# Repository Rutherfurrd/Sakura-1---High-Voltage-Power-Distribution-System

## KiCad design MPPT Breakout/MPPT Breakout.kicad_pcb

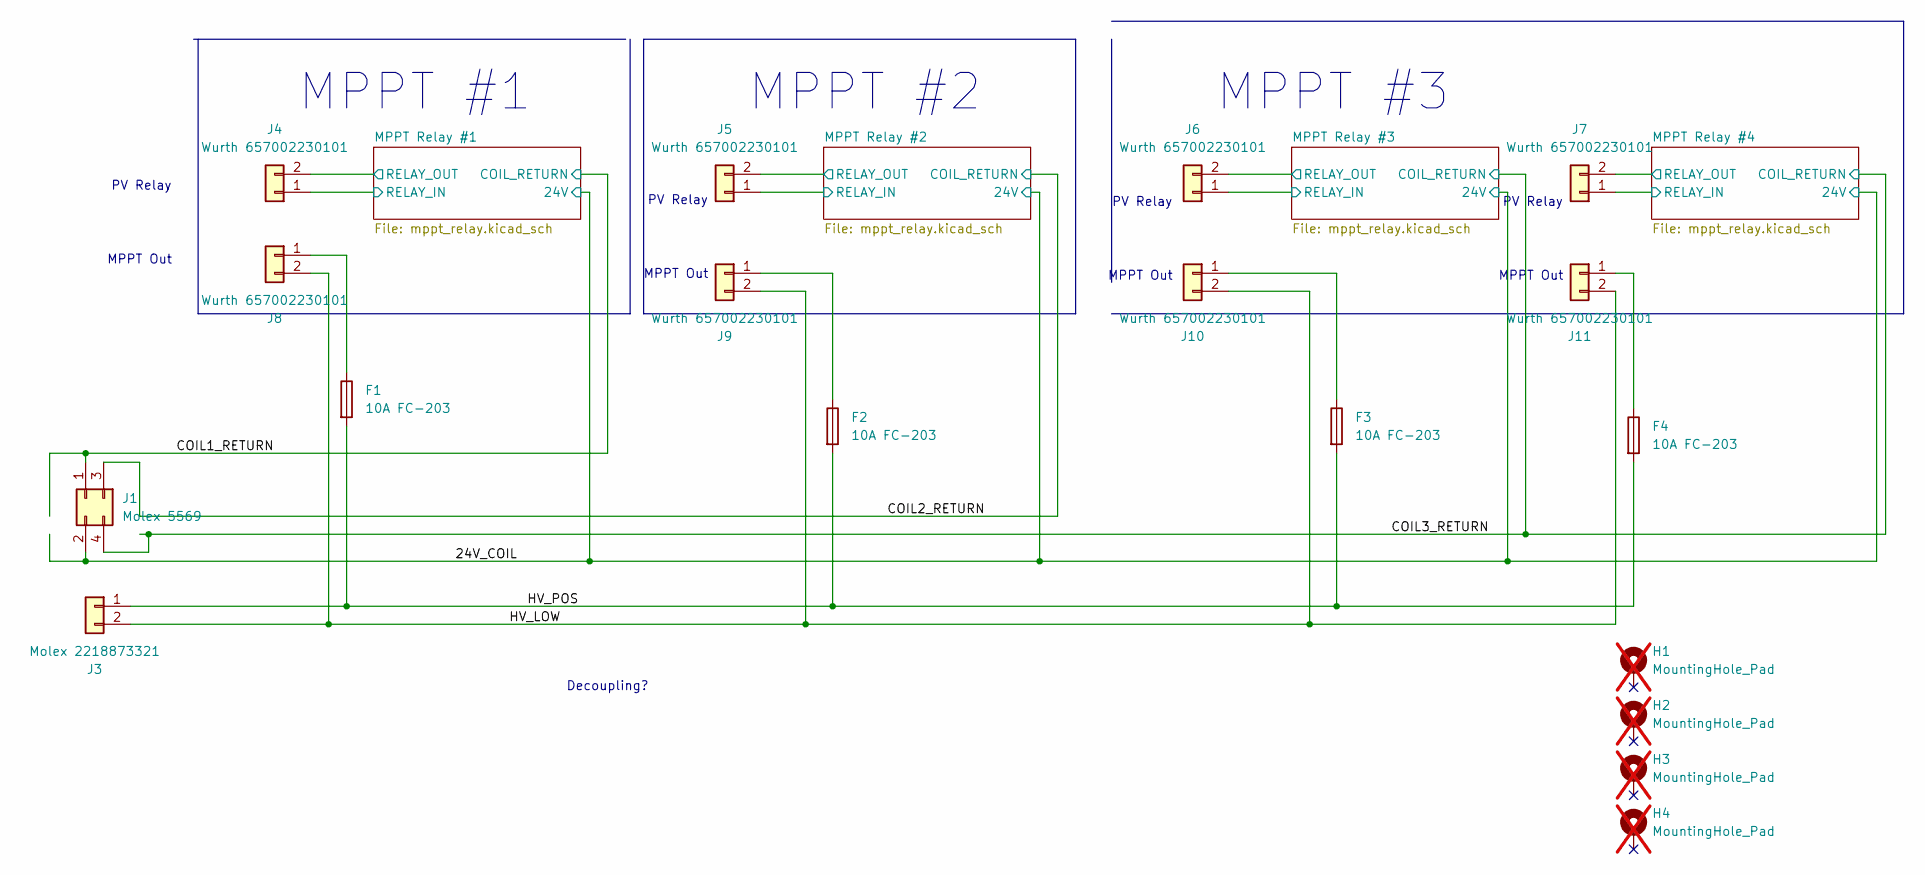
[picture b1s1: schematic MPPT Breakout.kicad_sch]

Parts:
F1, F2, F3, F4: 10A FC-203; Fuseholder_Clip-5x20mm_Bel_FC-203-22_Lateral_P17.80x5.00mm_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; Digikey SID 5923-FC-203BRIGHTTIN-ND
H1, H2, H3, H4: MountingHole_Pad; MountingHole_3.2mm_M3_DIN965_Pad_TopBottom; not fitted
J1: Molex 5569; Molex_Mini-Fit_Jr_5569-04A2_2x02_P4.20mm_Horizontal; Digikey SID WM23323-ND
J3: Molex 2218873321; CONN_2218873321_KEYOPT1_02P_MOL; Digikey SID 900-2218873321-ND
J4, J5, J6, J7, J8, J9, J10, J11: Wurth 657002230101; 657002230101; Digikey SID 732-657002230101-ND

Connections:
/24V_COIL: J1.2 (Pin_3); also elsewhere on the board
/COIL1_RETURN: J1.1 (Pin_2); also elsewhere on the board
/COIL2_RETURN: J1.3 (Pin_1); also elsewhere on the board
/COIL3_RETURN: J1.4; also elsewhere on the board
/HV_LOW: J3.2, J8.2, J9.2, J10.2, J11.2
/HV_POS: F1.2, F2.2, F3.2, F4.2, J3.1
/MPPT Relay #1/RELAY_IN: J4.1; also elsewhere on the board
/MPPT Relay #1/RELAY_OUT: J4.2; also elsewhere on the board
/MPPT Relay #2/RELAY_IN: J5.1; also elsewhere on the board
/MPPT Relay #2/RELAY_OUT: J5.2; also elsewhere on the board
/MPPT Relay #3/RELAY_IN: J6.1; also elsewhere on the board
/MPPT Relay #3/RELAY_OUT: J6.2; also elsewhere on the board
/MPPT Relay #4/RELAY_IN: J7.1; also elsewhere on the board
/MPPT Relay #4/RELAY_OUT: J7.2; also elsewhere on the board
unnamed: F1.1, J8.1
unnamed: F2.1, J9.1
unnamed: F3.1, J10.1
unnamed: F4.1, J11.1

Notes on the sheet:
MPPT Out
Decoupling?
MPPT #3
PV Relay
MPPT #1
MPPT #2

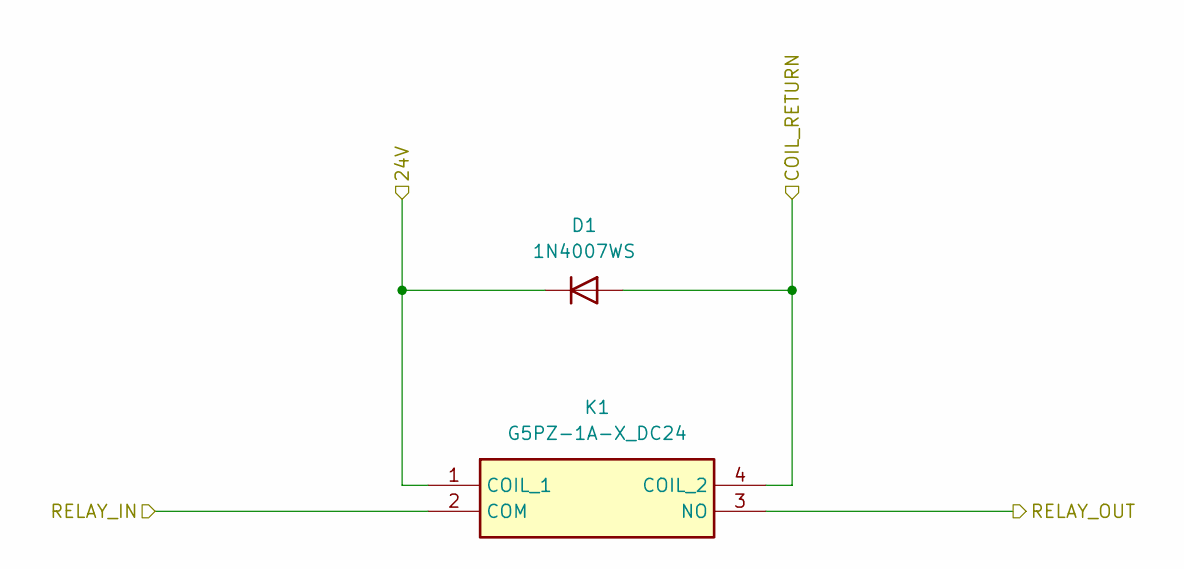
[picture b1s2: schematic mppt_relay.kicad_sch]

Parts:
D1: 1N4007WS; D_SOD-323_HandSoldering; Digikey SID 5399-1N4007WSCT-ND
K1: G5PZ-1A-X_DC24; G5PZ1AXDC24; Mouser Part Number 653-G5PZ-1A-XDC24

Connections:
/24V_COIL: D1.1 (K), K1.1 (COIL_1); also elsewhere on the board
/COIL1_RETURN: D1.2 (A), K1.4 (COIL_2); also elsewhere on the board
/MPPT Relay #1/RELAY_IN: K1.2 (COM); also elsewhere on the board
/MPPT Relay #1/RELAY_OUT: K1.3 (NO); also elsewhere on the board

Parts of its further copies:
D2, D3, D4: 1N4007WS; D_SOD-323_HandSoldering; Digikey SID 5399-1N4007WSCT-ND
K2, K3, K4: G5PZ-1A-X_DC24; G5PZ1AXDC24; Mouser Part Number 653-G5PZ-1A-XDC24

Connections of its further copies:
/24V_COIL: D2.1 (K), D3.1 (K), D4.1 (K), K2.1 (COIL_1), K3.1 (COIL_1), K4.1 (COIL_1); also elsewhere on the board
/COIL2_RETURN: D2.2 (A), K2.4 (COIL_2); also elsewhere on the board
/COIL3_RETURN: D3.2 (A), D4.2 (A), K3.4 (COIL_2), K4.4 (COIL_2); also elsewhere on the board
/MPPT Relay #2/RELAY_IN: K2.2 (COM); also elsewhere on the board
/MPPT Relay #2/RELAY_OUT: K2.3 (NO); also elsewhere on the board
/MPPT Relay #3/RELAY_IN: K3.2 (COM); also elsewhere on the board
/MPPT Relay #3/RELAY_OUT: K3.3 (NO); also elsewhere on the board
/MPPT Relay #4/RELAY_IN: K4.2 (COM); also elsewhere on the board
/MPPT Relay #4/RELAY_OUT: K4.3 (NO); also elsewhere on the board

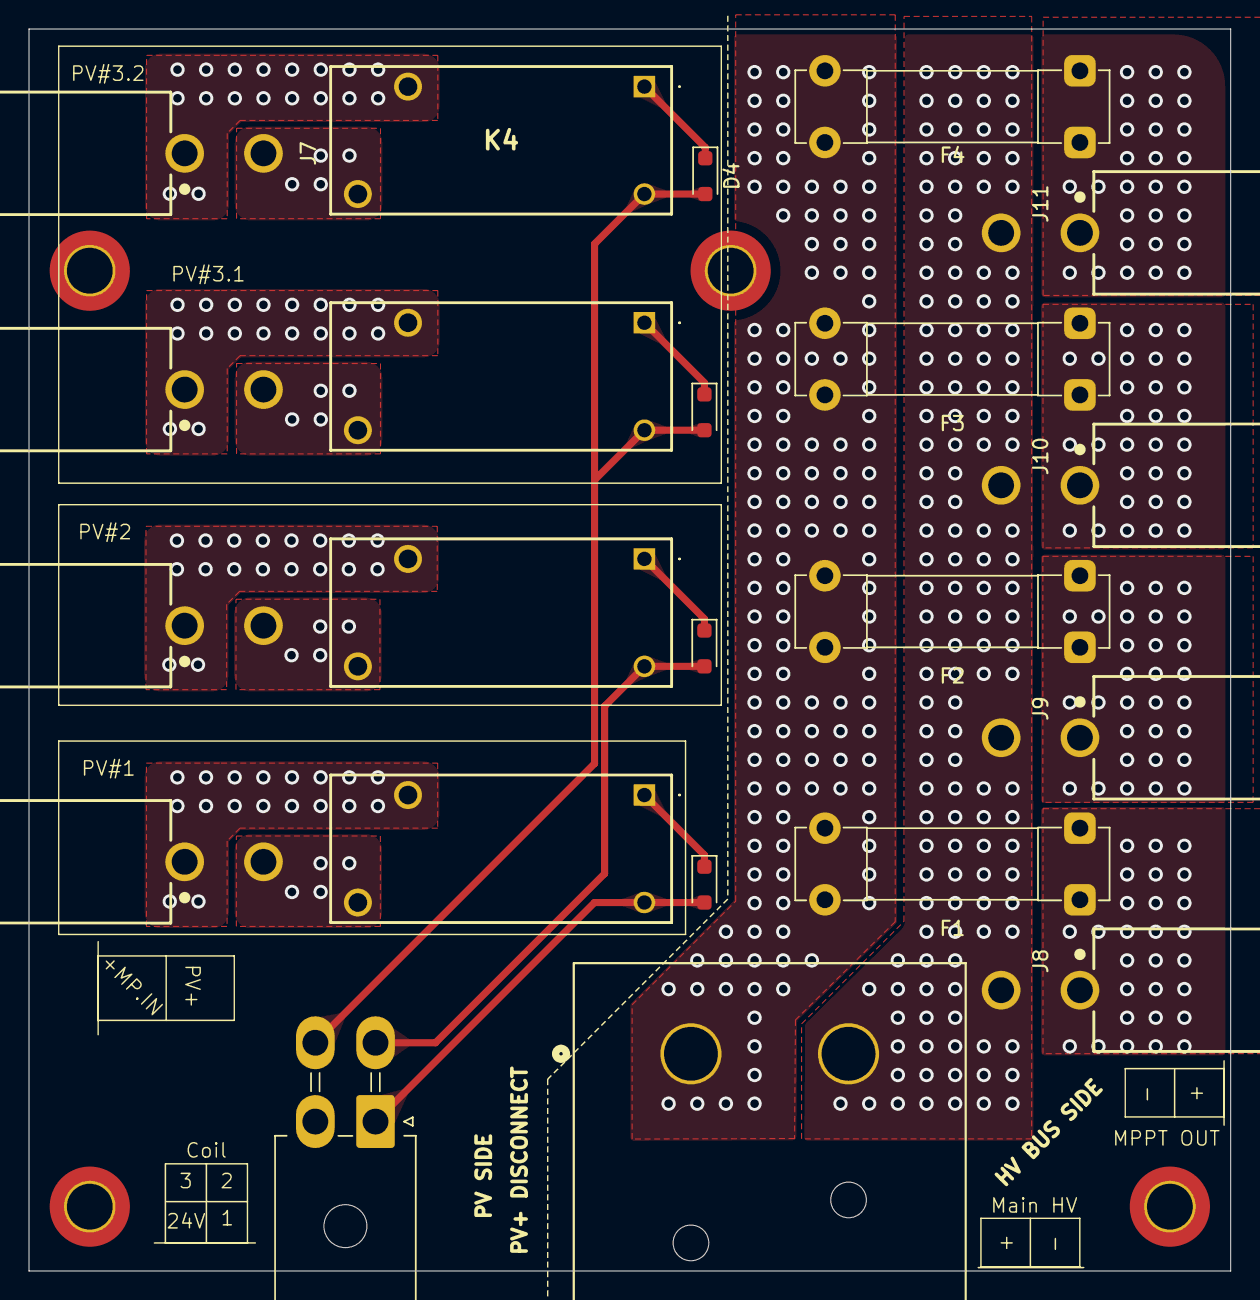
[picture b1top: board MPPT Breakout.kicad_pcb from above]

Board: 4 copper layers, 83.9 x 86.7 mm, 26 parts (0 on the bottom side), 18 nets.

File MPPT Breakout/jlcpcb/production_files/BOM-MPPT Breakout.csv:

Comment,Designator,Footprint,LCSC,Quantity
Wurth 657002230101,J5,657002230101,,1
10A FC-203,F3,Fuseholder_Clip-5x20mm_Bel_FC-203-22_Lateral_P17.80x5.00mm_D1.17mm_Horizontal,,1
10A FC-203,F1,Fuseholder_Clip-5x20mm_Bel_FC-203-22_Lateral_P17.80x5.00mm_D1.17mm_Horizontal,,1
1N4007WS,D2,D_SOD-323_HandSoldering,,1
Wurth 657002230101,J4,657002230101,,1
Wurth 657002230101,J6,657002230101,,1
Molex 2218873321,J3,CONN_2218873321_KEYOPT1_02P_MOL,,1
10A FC-203,F2,Fuseholder_Clip-5x20mm_Bel_FC-203-22_Lateral_P17.80x5.00mm_D1.17mm_Horizontal,,1
Molex 5569,J1,Molex_Mini-Fit_Jr_5569-04A2_2x02_P4.20mm_Horizontal,,1
1N4007WS,D3,D_SOD-323_HandSoldering,,1
1N4007WS,D1,D_SOD-323_HandSoldering,,1
1N4007WS,D4,D_SOD-323_HandSoldering,,1
10A FC-203,F4,Fuseholder_Clip-5x20mm_Bel_FC-203-22_Lateral_P17.80x5.00mm_D1.17mm_Horizontal,,1
Wurth 657002230101,J7,657002230101,,1
Wurth 657002230101,J8,657002230101,,1
Wurth 657002230101,J10,657002230101,,1
Wurth 657002230101,J11,657002230101,,1
Wurth 657002230101,J9,657002230101,,1

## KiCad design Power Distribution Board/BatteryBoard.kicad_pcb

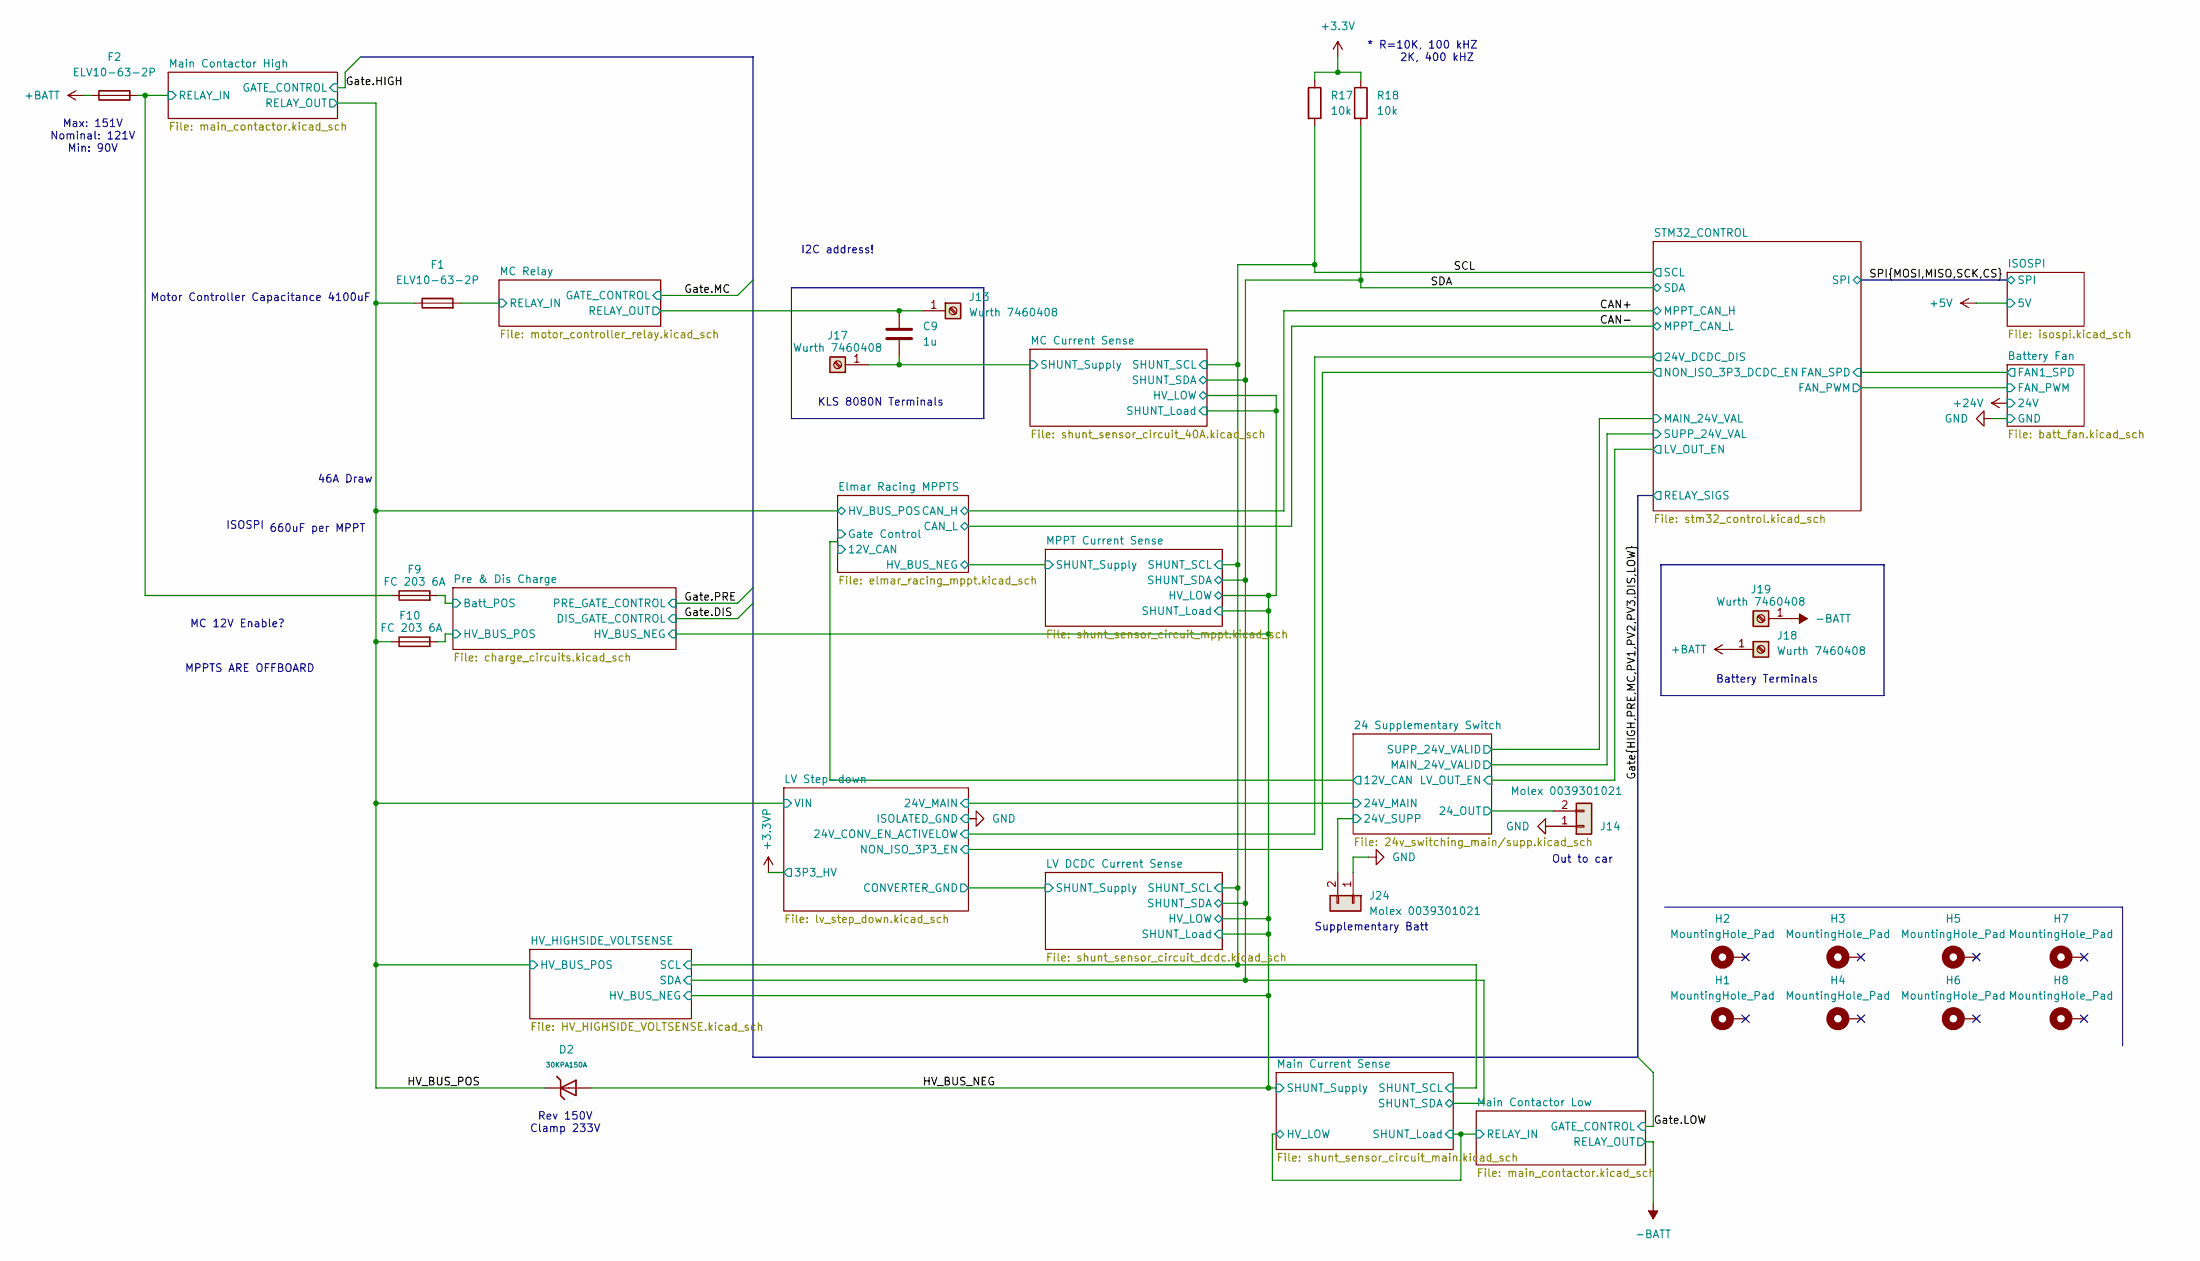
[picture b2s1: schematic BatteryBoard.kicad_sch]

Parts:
C9: 1u; C_1812_4532Metric; LCSC C3037685
D2: 30KPA150A; D_P600_R-6_P7.62mm_Vertical_AnodeUp; DigiKey_Part_Number 30KPA150ACT-ND
F1, F2: ELV10-63-2P; ELV10-XX-2P; DigiKey_Part_Number 283-ELV10-63-2P-ND
F9, F10: FC 203 6A; Fuseholder_Clip-5x20mm_Bel_FC-203-22_Lateral_P17.80x5.00mm_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; DigiKey_Part_Number 5923-FC-203BRIGHTTIN-ND
H1, H2, H3, H4, H5, H6, H7, H8: MountingHole_Pad; MountingHole_3.2mm_M3_DIN965_Pad_TopBottom
J13, J17, J18, J19: Wurth 7460408; MP_Wurth_WP-BUCF_7460408; DigiKey_Part_Number 732-7460408-ND
J14, J24: Molex 0039301021; Molex_Mini-Fit_Jr_5566-02A_2x01_P4.20mm_Vertical; DigiKey_Part_Number WM3843-ND
R17, R18: 10k; R_0603_1608Metric_Pad0.98x0.95mm_HandSolder; Rating 75V; LCSC C95204

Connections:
+3.3V: R17.1, R18.1; also elsewhere on the board
+BATT: F2.1, J18.1 (Pin_1_1)
-BATT: J19.1 (Pin_1_1); also elsewhere on the board
/24 Supplementary Switch/24V_SUPP: J24.2; also elsewhere on the board
/24 Supplementary Switch/24_OUT: J14.2; also elsewhere on the board
/<NO NET>: R17.2; also elsewhere on the board
/HV_BUS_NEG: D2.2; also elsewhere on the board
/HV_BUS_POS: D2.1, F1.1, F10.1; also elsewhere on the board
/MC Current Sense/SHUNT_Supply: C9.2, J17.1 (Pin_1_1); also elsewhere on the board
/MC Relay/RELAY_IN: F1.2; also elsewhere on the board
/MC Relay/RELAY_OUT: C9.1, J13.1 (Pin_1_1); also elsewhere on the board
/Main Contactor High/RELAY_IN: F2.2, F9.1; also elsewhere on the board
/Pre & Dis Charge/Batt_POS: F9.2; also elsewhere on the board
/Pre & Dis Charge/HV_BUS_POS: F10.2; also elsewhere on the board
/SDA: R18.2; also elsewhere on the board
GND: J14.1, J24.1; also elsewhere on the board

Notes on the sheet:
ISOSPI
MPPTS ARE OFFBOARD
Supplementary Batt
Out to car
MC 12V Enable?
Motor Controller Capacitance 4100uF
I2C address!
660uF per MPPT
Rev 150V Clamp 233V
* R=10K, 100 kHZ 2K, 400 kHZ
KLS 8080N Terminals
Max: 151V Nominal: 121V Min: 90V
Battery Terminals
46A Draw

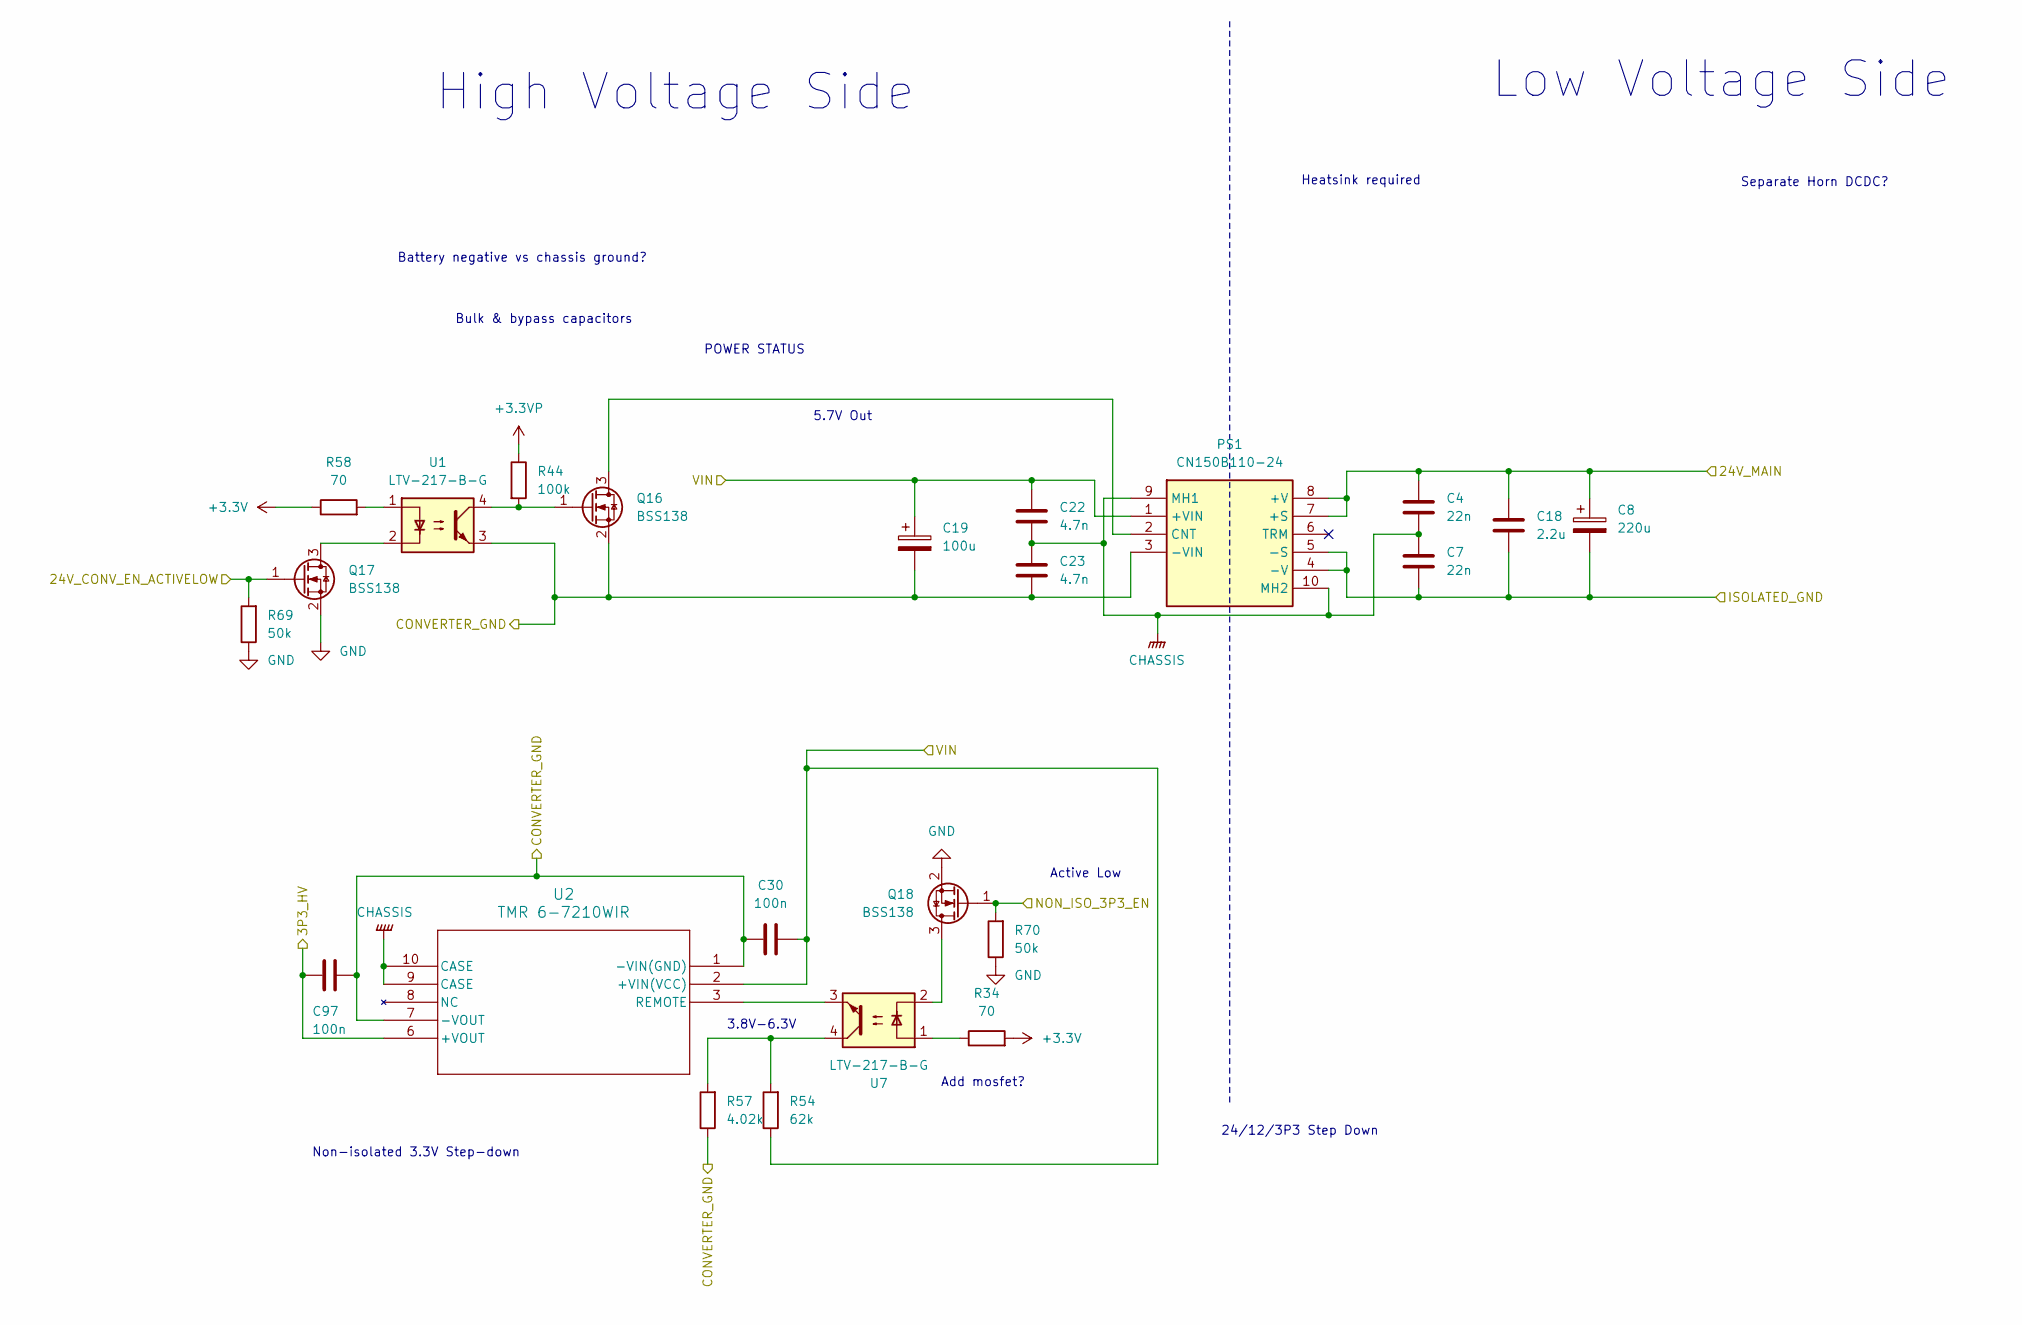
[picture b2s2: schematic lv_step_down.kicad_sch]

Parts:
C4, C7: 22n; R_0805_2012Metric; LCSC C1729
C8: 220u; CP_Radial_D10.0mm_P5.00mm; DigiKey_Part_Number CAP ALUM 220UF 20% 50V RADIAL TH
C18: 2.2u; C_0805_2012Metric_Pad1.18x1.45mm_HandSolder; LCSC C377773
C19: 100u; CP_Radial_D16.0mm_P7.50mm; DigiKey_Part_Number UCS2E101MHD
C22, C23: 4.7n; C_1206_3216Metric_Pad1.33x1.80mm_HandSolder; LCSC C106075
C30: 100n; C_1206_3216Metric_Pad1.33x1.80mm_HandSolder; LCSC C76671
C97: 100n; C_0603_1608Metric_Pad1.08x0.95mm_HandSolder; Rating 50V; LCSC C14663
PS1: CN150B110-24; CN100B11024; Mouser Part Number 967-CN100B110-24
Q16, Q17, Q18: BSS138; SOT-23; LCSC C7420339
R34, R58: 70; R_0603_1608Metric_Pad0.98x0.95mm_HandSolder; Rating 70V; LCSC C4275
R44: 100k; R_0603_1608Metric_Pad0.98x0.95mm_HandSolder; LCSC C25803
R54: 62k; C_0603_1608Metric_Pad1.08x0.95mm_HandSolder; Rating 200V; LCSC C403521
R57: 4.02k; R_0603_1608Metric_Pad0.98x0.95mm_HandSolder; Rating 75V; LCSC C242164
R69, R70: 50k; R_0603_1608Metric_Pad0.98x0.95mm_HandSolder; Rating 70V; LCSC C23184
U1, U7: LTV-217-B-G; SOP-4_4.4x2.6mm_P1.27mm; Part LTV-217-B-G; LCSC C115450
U2: TMR 6-7210WIR; TMR6WIR-SINGLE_TRP; DigiKey_Part_Number 1951-2031-ND

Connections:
+3.3V: R34.2, R58.1; also elsewhere on the board
+3.3VP: C97.2, R44.1, U2.6 (+VOUT); also elsewhere on the board
/24 Supplementary Switch/24V_MAIN: C4.1, C8.1, C18.1, PS1.7 (+S), PS1.8 (+V); also elsewhere on the board
/HV_BUS_POS: C19.1, C22.1, C30.1, PS1.1 (+VIN), R54.1, U2.2 (+VIN(VCC)); also elsewhere on the board
/LV DCDC Current Sense/SHUNT_Supply: C19.2, C23.2, C30.2, C97.1, PS1.3 (-VIN), Q16.2 (S), R57.1, U1.3, U2.1 (-VIN(GND)), U2.7 (-VOUT); also elsewhere on the board
/LV Step-down/24V_CONV_EN_ACTIVELOW: Q17.1 (G), R69.2; also elsewhere on the board
/LV Step-down/NON_ISO_3P3_EN: Q18.1 (G), R70.2; also elsewhere on the board
CHASSIS: C4.2, C7.1, C22.2, C23.1, PS1.9 (MH1), PS1.10 (MH2), U2.9 (CASE), U2.10 (CASE)
GND: C7.2, C8.2, C18.2, PS1.4 (-V), PS1.5 (-S), Q17.2 (S), Q18.2 (S), R69.1, R70.1; also elsewhere on the board
unnamed: PS1.2 (CNT), Q16.3 (D)
unnamed: Q16.1 (G), R44.2, U1.4
unnamed: Q17.3 (D), U1.2
unnamed: Q18.3 (D), U7.2
unnamed: R34.1, U7.1
unnamed: R54.2, R57.2, U7.4
unnamed: R58.2, U1.1
unnamed: U2.3 (REMOTE), U7.3

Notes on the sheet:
Active Low
Separate Horn DCDC?
Bulk & bypass capacitors
High Voltage Side
24/12/3P3 Step Down
Low Voltage Side
Battery negative vs chassis ground?
Add mosfet?
POWER STATUS
3.8V-6.3V
Non-isolated 3.3V Step-down
Heatsink required
5.7V Out

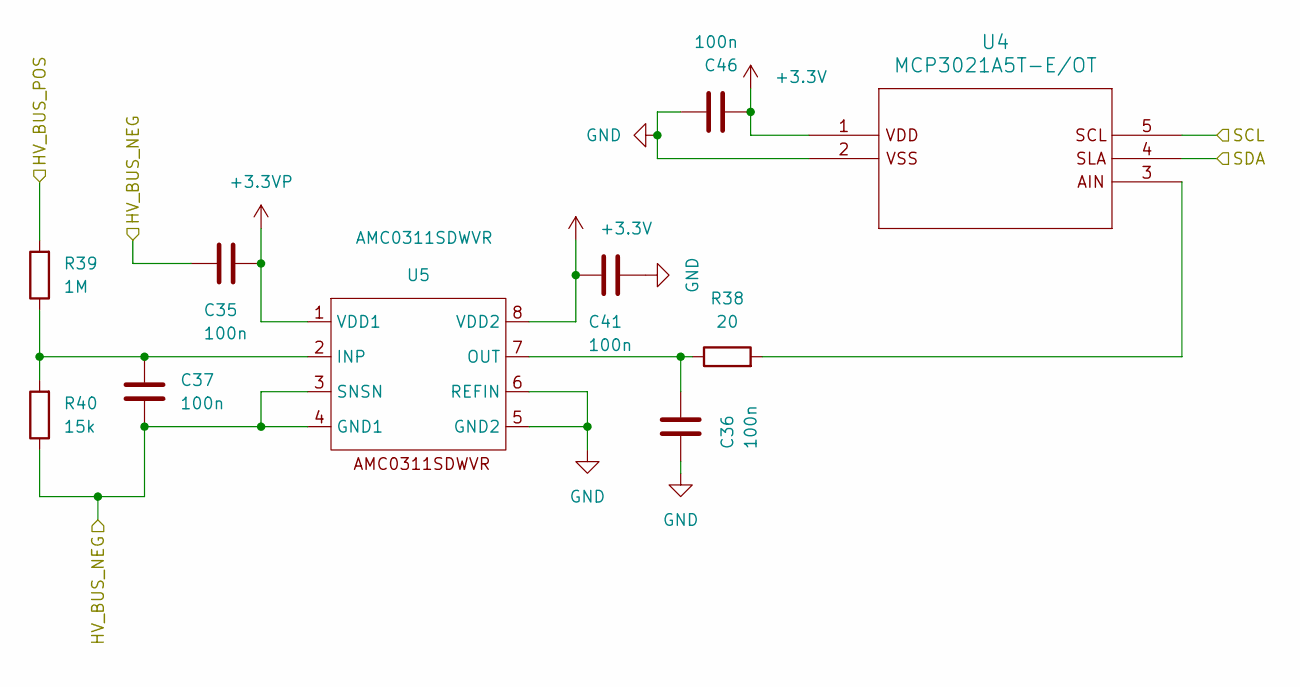
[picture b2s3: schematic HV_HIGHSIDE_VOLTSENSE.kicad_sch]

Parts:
C35, C36, C37, C41, C46: 100n; C_0603_1608Metric_Pad1.08x0.95mm_HandSolder; Rating 50V; LCSC C14663
R38: 20; R_0603_1608Metric_Pad0.98x0.95mm_HandSolder; Rating 75V; LCSC C22950
R39: 1M; R_1206_3216Metric_Pad1.30x1.75mm_HandSolder; Rating 200V; LCSC C17927
R40: 15k; C_0805_2012Metric; Rating 200V; LCSC C17475
U4: MCP3021A5T-E/OT; SOT-23-5; LCSC C128576
U5: AMC0311SDWVR; DWV0008A; LCSC C44211429

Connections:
+3.3V: C41.2, C46.2, U4.1, U5.8 (VDD2); also elsewhere on the board
+3.3VP: C35.1, U5.1 (VDD1); also elsewhere on the board
/<NO NET>: U4.5; also elsewhere on the board
/HV_BUS_NEG: C35.2, C37.2, R40.1, U5.3 (SNSN), U5.4 (GND1); also elsewhere on the board
/HV_BUS_POS: R39.2; also elsewhere on the board
/SDA: U4.4; also elsewhere on the board
GND: C36.2, C41.1, C46.1, U4.2, U5.5 (GND2), U5.6 (REFIN); also elsewhere on the board
unnamed: R38.2, U4.3
unnamed: C37.1, R39.1, R40.2, U5.2 (INP)
unnamed: C36.1, R38.1, U5.7 (OUT)

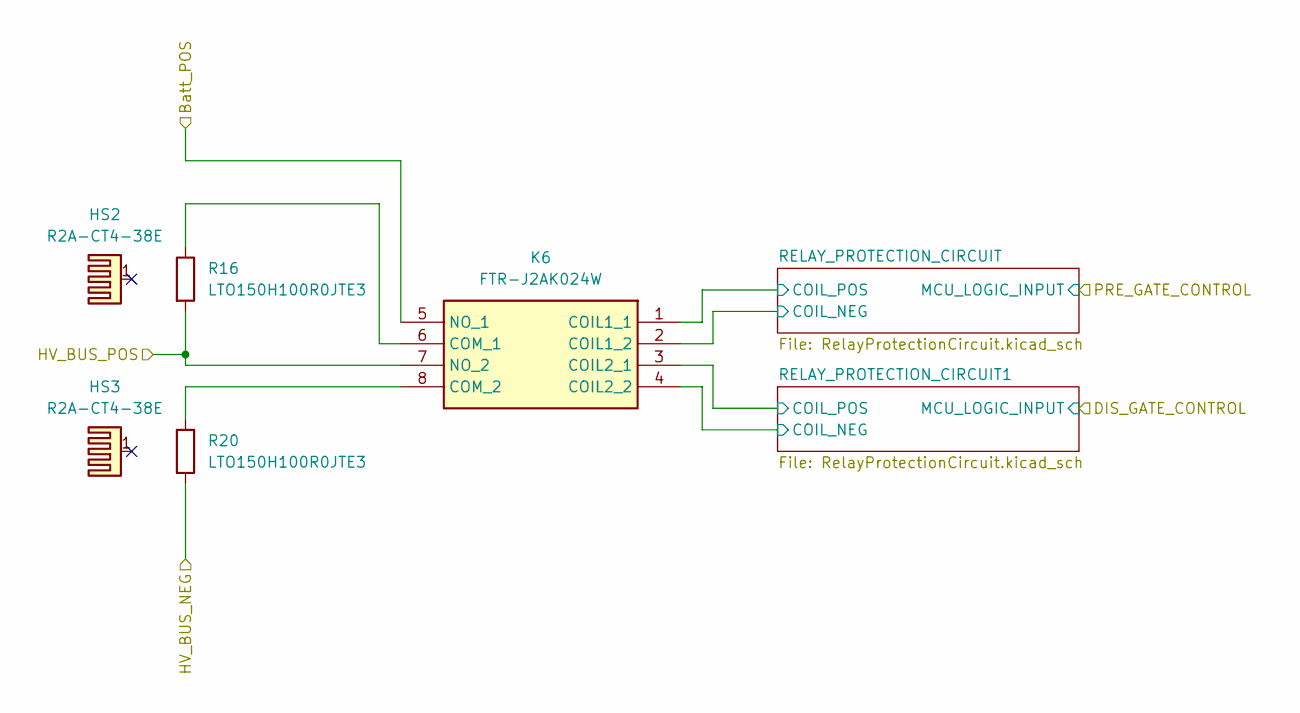
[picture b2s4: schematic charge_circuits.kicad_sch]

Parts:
HS2, HS3: R2A-CT4-38E; DigiKey_Part_Number R2A-CT4-38E-ND
K6: FTR-J2AK024W; FTRJ2AK012W; Mouser Part Number 817-FTR-J2AK012W
R16, R20: LTO150H100R0JTE3; TO-247-2_Vertical; DigiKey_Part_Number 716-LTO150H100R0JTE3-ND

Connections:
+24V: K6.1 (COIL1_1), K6.3 (COIL2_1); also elsewhere on the board
/HV_BUS_NEG: R20.2; also elsewhere on the board
/Pre & Dis Charge/Batt_POS: K6.5 (NO_1); also elsewhere on the board
/Pre & Dis Charge/HV_BUS_POS: K6.7 (NO_2), R16.2; also elsewhere on the board
/Pre & Dis Charge/RELAY_PROTECTION_CIRCUIT1/COIL_NEG: K6.4 (COIL2_2); also elsewhere on the board
/Pre & Dis Charge/RELAY_PROTECTION_CIRCUIT/COIL_NEG: K6.2 (COIL1_2); also elsewhere on the board
unnamed: K6.6 (COM_1), R16.1
unnamed: K6.8 (COM_2), R20.1

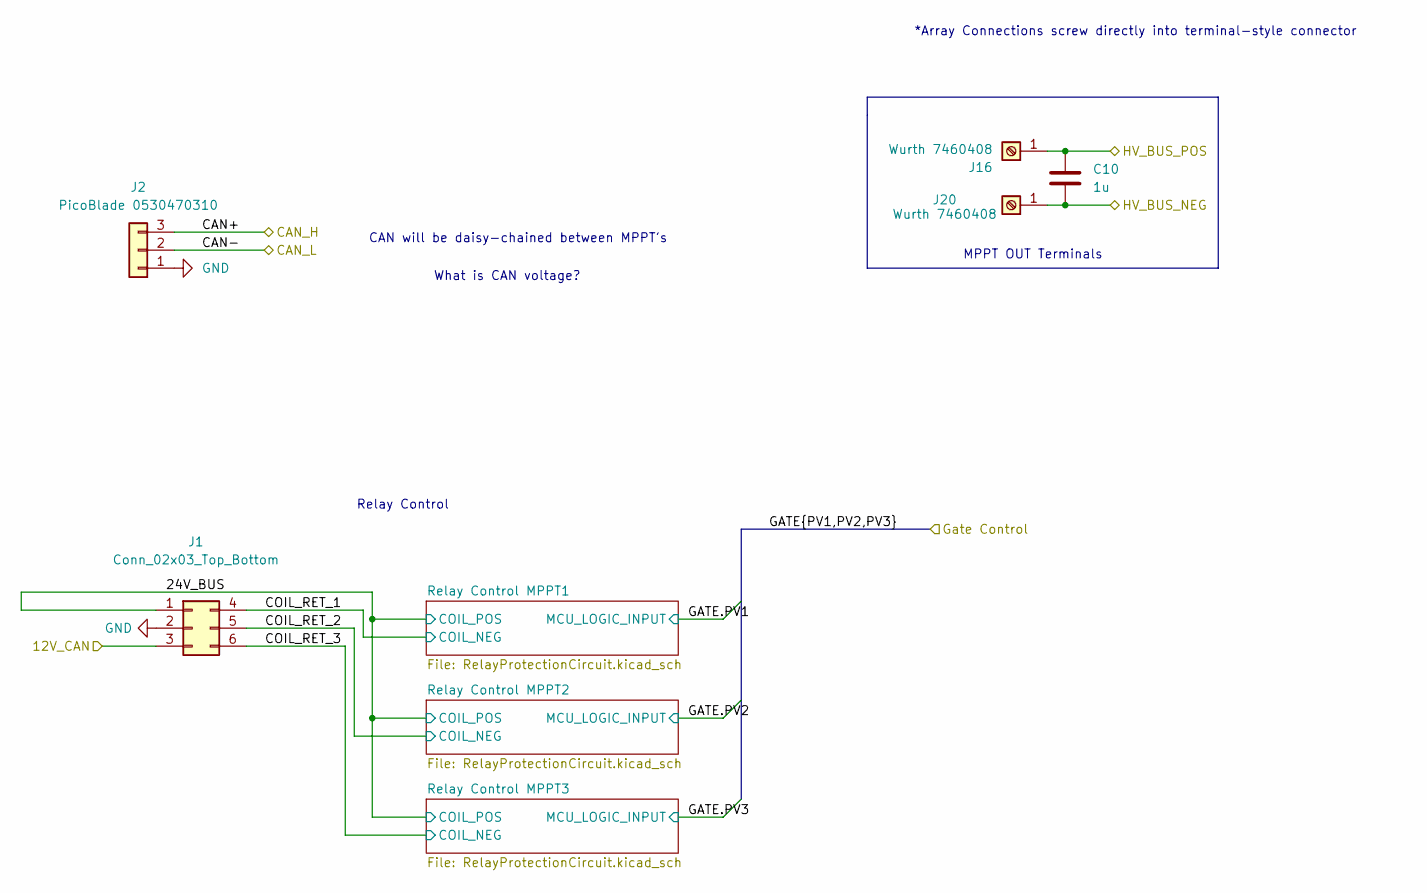
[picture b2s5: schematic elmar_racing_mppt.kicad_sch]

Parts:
C10: 1u; C_1812_4532Metric; LCSC C3037685
J1: Conn_02x03_Top_Bottom; Molex_Mini-Fit_Jr_5566-06A_2x03_P4.20mm_Vertical; DigiKey_Part_Number WM3802-ND
J2: PicoBlade 0530470310; Molex_PicoBlade_53047-0310_1x03_P1.25mm_Vertical; DigiKey_Part_Number WM1732-ND
J16, J20: Wurth 7460408; MP_Wurth_WP-BUCF_7460408; DigiKey_Part_Number 732-7460408-ND

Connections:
+24V: J1.1; also elsewhere on the board
/24 Supplementary Switch/12V_CAN: J1.3; also elsewhere on the board
/CAN+: J2.3; also elsewhere on the board
/CAN-: J2.2; also elsewhere on the board
/Elmar Racing MPPTS/COIL_RET_1: J1.4; also elsewhere on the board
/Elmar Racing MPPTS/COIL_RET_2: J1.5; also elsewhere on the board
/Elmar Racing MPPTS/COIL_RET_3: J1.6; also elsewhere on the board
/Elmar Racing MPPTS/HV_BUS_NEG: C10.2, J20.1 (Pin_1_1); also elsewhere on the board
/HV_BUS_POS: C10.1, J16.1 (Pin_1_1); also elsewhere on the board
GND: J1.2, J2.1; also elsewhere on the board

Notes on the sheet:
CAN will be daisy-chained between MPPT's
*Array Connections screw directly into terminal-style connector
MPPT OUT Terminals
What is CAN voltage?
Relay Control

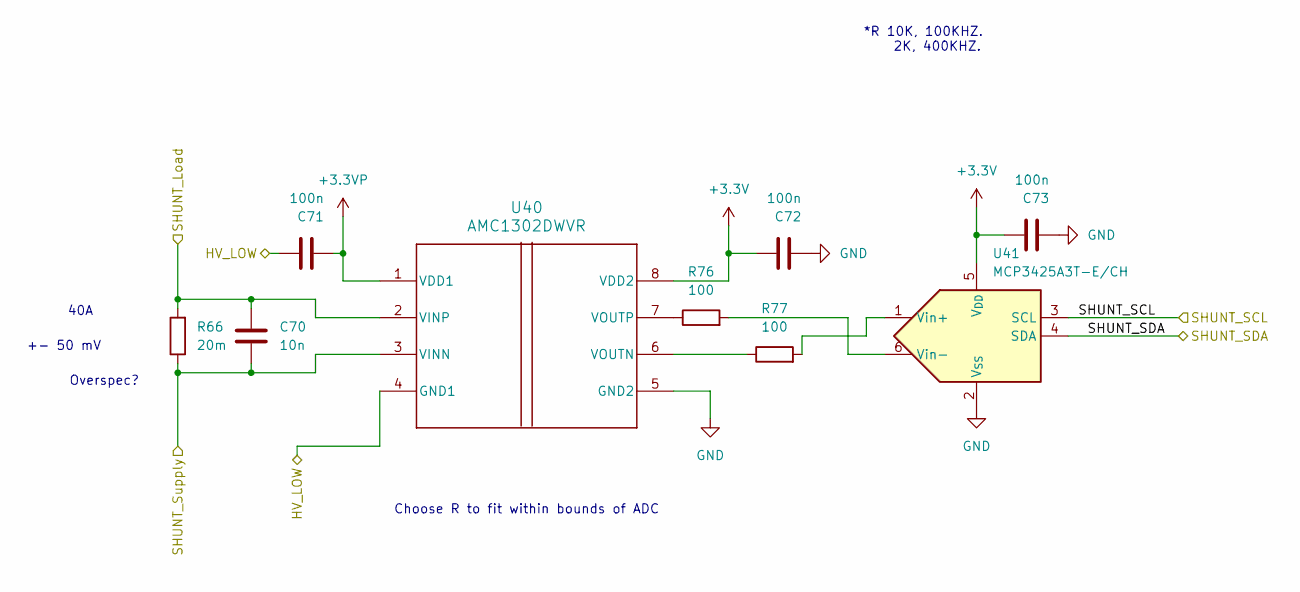
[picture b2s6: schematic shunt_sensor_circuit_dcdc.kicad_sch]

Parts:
C70: 10n; C_0603_1608Metric_Pad1.08x0.95mm_HandSolder; Rating 50V; LCSC C57112
C71, C72, C73: 100n; C_0603_1608Metric_Pad1.08x0.95mm_HandSolder; Rating 50V; LCSC C14663
R66: 20m; D_2512_6332Metric; Rating 200V; LCSC C845325
R76, R77: 100; R_0603_1608Metric_Pad0.98x0.95mm_HandSolder; Rating 75V; LCSC C22775
U40: AMC1302DWVR; DWV0008A; LCSC C2863209
U41: MCP3425A3T-E/CH; SOT-23-6; DigiKey_Part_Number 150-MCP3425A3T-E/CHDKR-ND

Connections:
+3.3V: C72.1, C73.1, U40.8 (VDD2), U41.5 (V_{DD}); also elsewhere on the board
+3.3VP: C71.2, U40.1 (VDD1); also elsewhere on the board
/<NO NET>: U41.3 (SCL); also elsewhere on the board
/HV_BUS_NEG: C70.1, C71.1, R66.2, U40.2 (VINP), U40.4 (GND1); also elsewhere on the board
/LV DCDC Current Sense/SHUNT_Supply: C70.2, R66.1, U40.3 (VINN); also elsewhere on the board
/SDA: U41.4 (SDA); also elsewhere on the board
GND: C72.2, C73.2, U40.5 (GND2), U41.2 (V_{SS}); also elsewhere on the board
unnamed: R77.1, U40.6 (VOUTN)
unnamed: R76.1, U40.7 (VOUTP)
unnamed: R77.2, U41.1 (Vin+)
unnamed: R76.2, U41.6 (Vin-)

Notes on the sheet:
Overspec?
40A
*R 10K, 100KHZ. 2K, 400KHZ.
Choose R to fit within bounds of ADC
+- 50 mV
